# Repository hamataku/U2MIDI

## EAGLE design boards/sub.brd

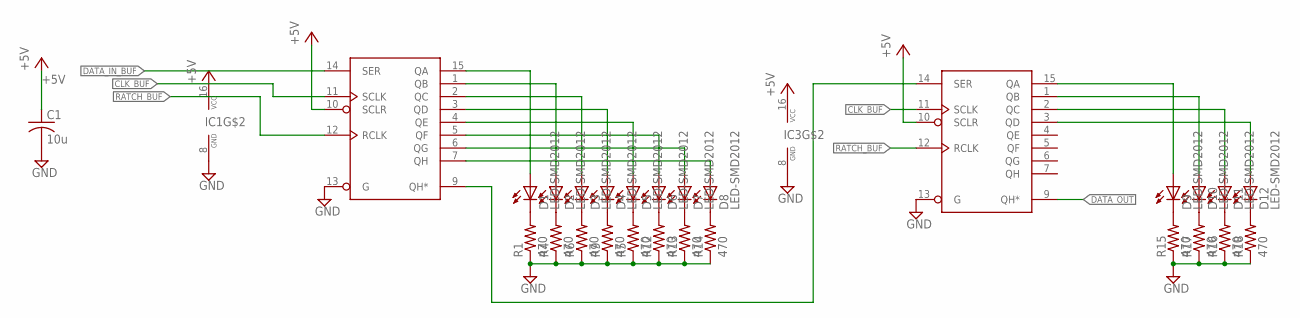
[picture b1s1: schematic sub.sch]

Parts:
C1: 10u; 2012-C
D1, D2, D3, D4, D5, D6, D7, D8, D9, D10, D11, D12: LED-SMD2012; D2012
IC1, IC3: 74595AP; SOP16
R1, R4, R5, R6, R9, R12, R13, R14, R15, R16, R17, R18: 470; 2012-R

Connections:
+5V: C1.1, IC1.10 (SCLR), IC1.16 (VCC), IC3.10 (SCLR), IC3.16 (VCC)
CLK_BUF: IC1.11 (SCLK), IC3.11 (SCLK)
DATA_IN_BUF: IC1.14 (SER)
DATA_OUT: IC3.9 (QH*)
GND: C1.2, IC1.8 (GND), IC1.13 (G), IC3.8 (GND), IC3.13 (G), R1.1, R4.1, R5.1, R6.1, R9.1, R12.1, R13.1, R14.1, R15.1, R16.1, R17.1, R18.1
unnamed: D1.K, R1.2
unnamed: D5.K, R5.2
unnamed: D2.K, R4.2
unnamed: D3.K, R6.2
unnamed: D4.K, R9.2
unnamed: D6.K, R12.2
unnamed: D7.K, R13.2
unnamed: D8.K, R14.2
unnamed: D1.A, IC1.15 (QA)
unnamed: D2.A, IC1.1 (QB)
unnamed: D3.A, IC1.2 (QC)
unnamed: D4.A, IC1.3 (QD)
unnamed: D5.A, IC1.4 (QE)
unnamed: D6.A, IC1.5 (QF)
unnamed: D7.A, IC1.6 (QG)
unnamed: D8.A, IC1.7 (QH)
unnamed: D9.K, R15.2
unnamed: D10.K, R17.2
unnamed: D11.K, R16.2
unnamed: D12.K, R18.2
unnamed: D9.A, IC3.15 (QA)
unnamed: D10.A, IC3.1 (QB)
unnamed: D11.A, IC3.2 (QC)
unnamed: D12.A, IC3.3 (QD)
unnamed: IC1.9 (QH*), IC3.14 (SER)
RATCH_BUF: IC1.12 (RCLK), IC3.12 (RCLK)

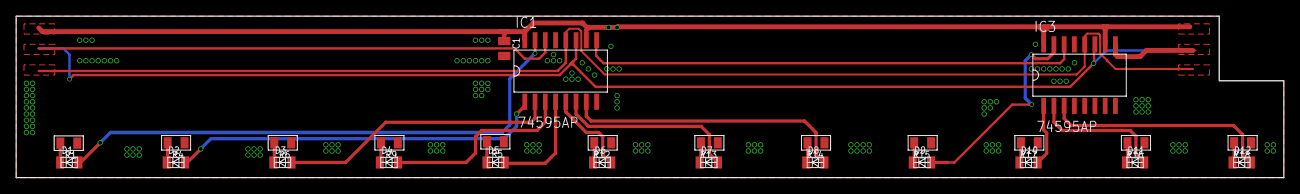
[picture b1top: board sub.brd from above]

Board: 2 copper layers, 157.0 x 20.0 mm, 27 parts (0 on the bottom side), 29 nets.

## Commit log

2023-02-22 in the middle of board design
2023-02-23 update board design
2023-02-26 First commit
    OpenCV.jsとWebMIDIのテスト
2023-02-28 webmidiで出力できるようになった
    外部MIDIデバイスにMIDI信号を送れるようになった
2023-03-01 Firmware compiled successfully
2023-03-01 Successfully turned stm32f4 into USB MIDI
2023-03-04 AB再生を実装
2023-03-06 midi通信に成功！
2023-03-07 LED glows at startup
2023-03-09 動画に合わせて規定プロトコルのMIDI信号を送れる
2023-03-10 added a bar detection code
2023-03-11 added a bar detection code for Kajiosan to convert
2023-03-11 implement hough transform
2023-03-11 implement getKeyPosition()
2023-03-12 analyzed the video and uplight lit up
2023-03-13 test
2023-03-13 README編集
2023-03-13 note 0
2023-03-13 Automatic detection of Uplight
2023-03-13 Implementation of octave adjustment function
2023-03-13 make key_default_color from key_list
2023-03-13 raised threshold
2023-03-14 UI改善
2023-03-15 change bootstrap version to 5 & remove dependency on jquery
2023-03-15 再生速度の調整機能実装
2023-03-18 made video display stylish
2023-03-18 solved #3 and #8 at once.
2023-03-18 make setting menu stylish
2023-03-18 Revert "solved #3 and #8 at once."
    This reverts commit 26600bb486322d5b8abec8cfb0b04c491b589928.
2023-03-18 apply commit 'solved #3 and #8 at once.'
2023-03-18 add practice mode
2023-03-19 setting view port
2023-03-20 test
    test
2023-03-21 解析失敗＆機器接続のアラートを追加
2023-03-21 Video can be stopped even in practice mode
2023-03-21 bug fix
2023-03-22 Changed browser name
    Changed browser name
2023-03-22 Added videos
    Added videos
2023-03-22 add components
2023-03-22 大枠の作成
2023-03-24 練習モード実装
2023-03-24 本番ページの大枠だけ実装
    違うブランチでやるべきでした…
2023-03-24 opencvjsのloadをasyncにしてみた
2023-03-24 デザインの微調整
2023-03-25 ビリーブは動く
2023-03-25 さんぽ以外は動作する
2023-03-25 videoの末尾を削除
2023-03-25 採点機能の実装done
2023-03-25 オンライン機能実装できてしまった
2023-03-26 動画アップロード機能復活
    間違えてdevelopで作業してしまいました…
2023-03-26 オンライン通話へのリンクをindexに設置
2023-03-27 鍵盤認識の線を太くした
2023-03-27 pushテスト
2023-03-27 デザイン調整
2023-03-28 Vuplight
2023-03-28 画面幅変更
2023-03-28 jquery削除
